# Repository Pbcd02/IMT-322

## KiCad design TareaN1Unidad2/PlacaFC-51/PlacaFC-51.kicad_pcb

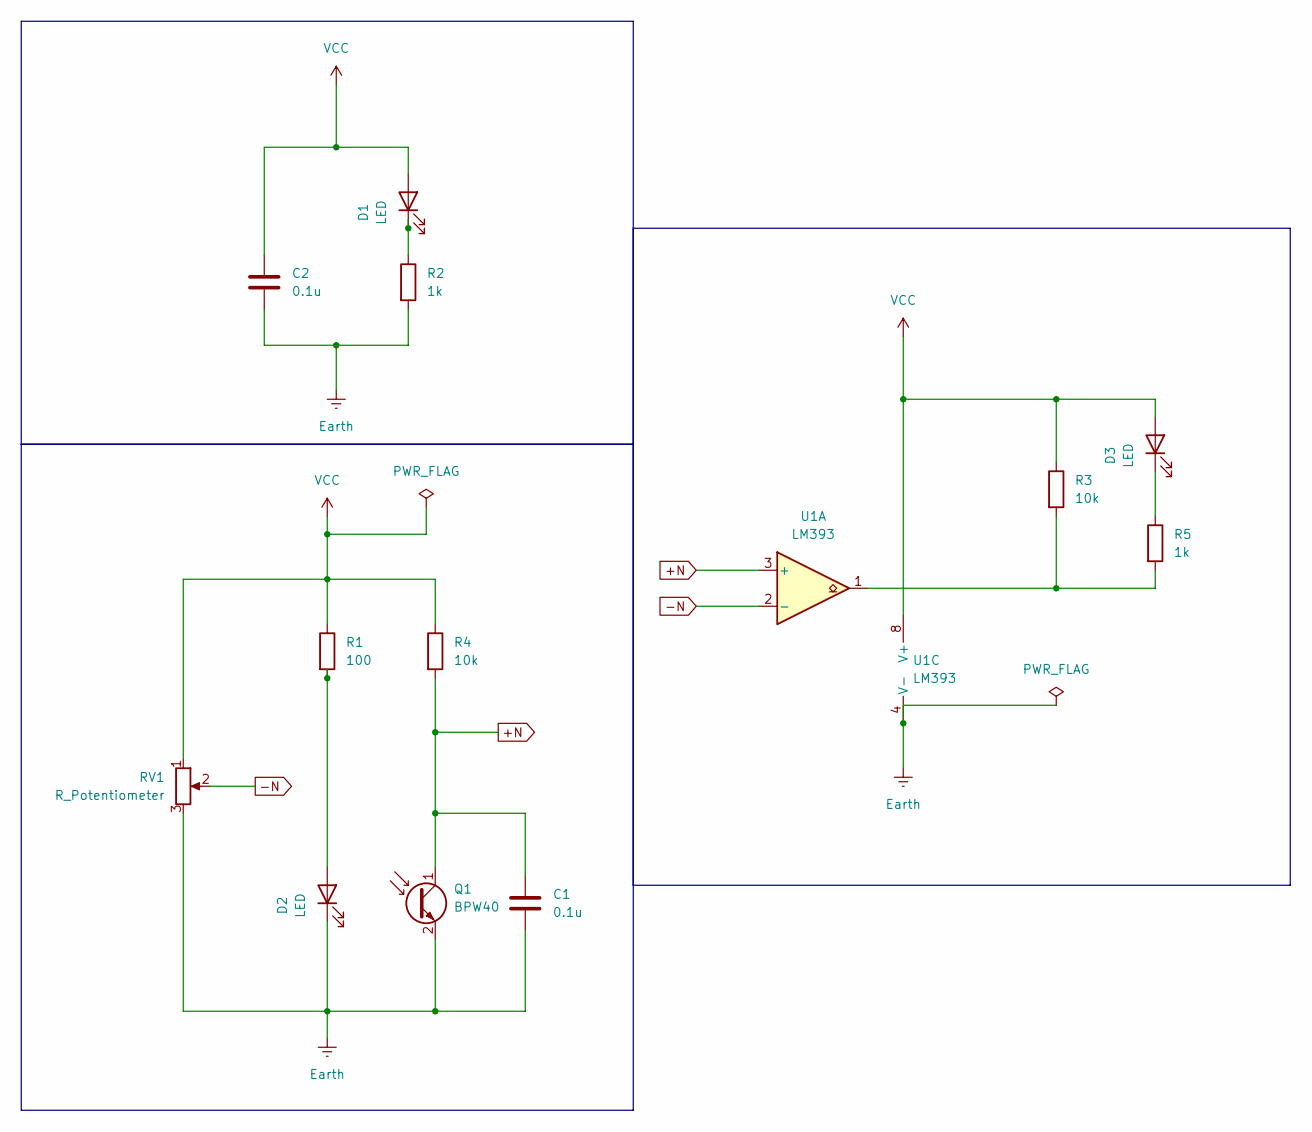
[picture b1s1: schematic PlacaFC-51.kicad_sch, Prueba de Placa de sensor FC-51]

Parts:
C1: 0.1u; C_0603_1608Metric_Pad1.08x0.95mm_HandSolder
C2: 0.1u; C_0603_1608Metric
D1, D2: LED; LED_miniPLCC_2315_Handsoldering
D3: LED; LED_D3.0mm_Horizontal_O1.27mm_Z2.0mm_Clear
Q1: BPW40; LED_D3.0mm_Horizontal_O1.27mm_Z2.0mm_IRBlack
R1: 100; R_0805_2012Metric_Pad1.20x1.40mm_HandSolder
R2, R5: 1k; R_0805_2012Metric_Pad1.20x1.40mm_HandSolder
R3, R4: 10k; R_0805_2012Metric_Pad1.20x1.40mm_HandSolder
RV1: R_Potentiometer; Potentiometer_Bourns_3314G_Vertical
U1: LM393; DIP-8_W7.62mm_SMDSocket_SmallPads

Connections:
+N: C1.1, Q1.1 (C), R4.2, U1.3 (+)
-N: RV1.2, U1.2 (-)
Earth: C1.2, C2.2, D2.1 (K), Q1.2 (E), R2.2, RV1.3, U1.4 (V-)
unnamed: D1.1 (K), R2.1
unnamed: D2.2 (A), R1.2
unnamed: D3.1 (K), R5.1
unnamed: R3.2, R5.2, U1.1
VCC: C2.1, D1.2 (A), D3.2 (A), R1.1, R3.1, R4.1, RV1.1, U1.8 (V+)

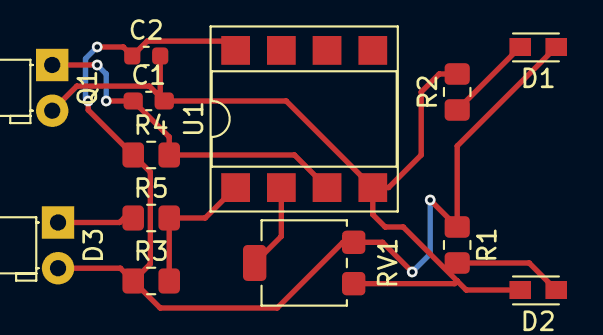
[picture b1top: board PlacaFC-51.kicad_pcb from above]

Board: 2 copper layers, 13 parts (0 on the bottom side), 8 nets.

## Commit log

2024-02-17 Agregando
2024-02-24 practica N1
2024-02-24 Practica1
2024-03-02 Subiendo
2024-03-09 CorrecionRepositorio
2024-03-19 Actualizacion de Repositorio
2024-03-19 SubiendoExamen
2024-04-12 Añadiendo repositorio
2024-04-21 actualizando repositorio
2024-04-22 Actualizando tarea de PCB
2024-04-29 ActualizandoYMejorando
2024-05-21 ActualizacionRepositorio
2024-05-23 Recuperatorio
2024-05-29 UltimoExamen
2024-06-01 Prototipado Rapido
